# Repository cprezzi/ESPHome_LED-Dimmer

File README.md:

## ESPHome LED-Dimmer

This PCB for crating an ESPHome based LED-Dimmer for 12V LED-Lights was made by KiCad 9.
The PCB is hosting an ESP32-C3 Supermini, a Mini Buck-Converter for 12V > 5V conversion and a Mosfet for PWM-switching the LEDs. 

ESPHome is used as the firmware on the ESP32-C3 (configured as PWM output).

The board is capable of driving LEDs up to 12V/5A.

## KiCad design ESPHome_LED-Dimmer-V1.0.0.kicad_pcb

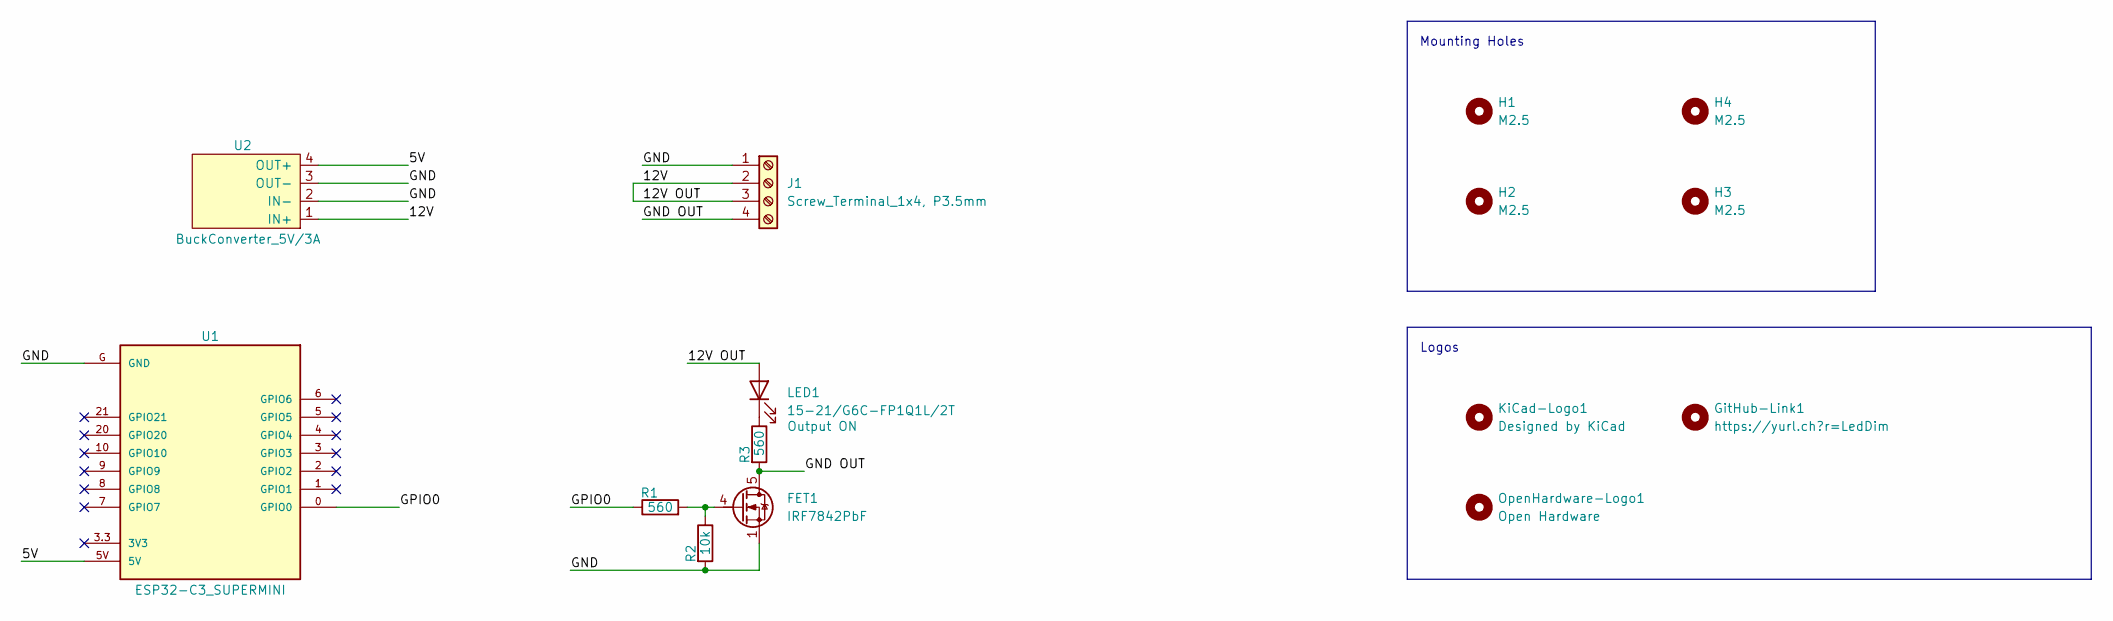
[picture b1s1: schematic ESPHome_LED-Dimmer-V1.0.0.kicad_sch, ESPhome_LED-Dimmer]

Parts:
FET1: IRF7842PbF; SOIC-8_3.9x4.9mm_P1.27mm
GitHub-Link1: https://yurl.ch?r=LedDim; QR_GitHub-LedDim
H1, H2, H3, H4: M2.5; MountingHole_2.2mm_M2
J1: Screw_Terminal_1x4, P3.5mm; TerminalBlock_MetzConnect_Type059_RT06304HBWC_1x04_P3.50mm_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
KiCad-Logo1: Designed by KiCad; KiCad-Logo2_5mm_SilkScreen
LED1: 15-21/G6C-FP1Q1L/2T; LED_1206_3216Metric
OpenHardware-Logo1: Open Hardware; OSHW-Logo2_7.3x6mm_SilkScreen
R1, R3: 560; R_XL_1206_3216Metric_Pad_HandSolder
R2: 10k; R_XL_1206_3216Metric_Pad_HandSolder
U1: ESP32-C3_SUPERMINI; MODULE_ESP32-C3_SUPERMINI_FlatSolder
U2: BuckConverter_5V/3A; Mini BuckConverter 5V 3A

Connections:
/5V: U1.5V, U2.4 (OUT+)
/12V: J1.2, J1.3, LED1.2 (A), U2.1 (IN+)
/GND: FET1.1 (S), FET1.2 (S), FET1.3 (S), J1.1, R2.2, U1.G (GND), U2.2 (IN-), U2.3 (OUT-)
/GND OUT: FET1.5 (D), FET1.6 (D), FET1.7 (D), FET1.8 (D), J1.4, R3.2
/GPIO0: R1.1, U1.0 (GPIO0)
unnamed: FET1.4 (G), R1.2, R2.1
unnamed: LED1.1 (K), R3.1

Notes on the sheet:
Logos
Mounting Holes

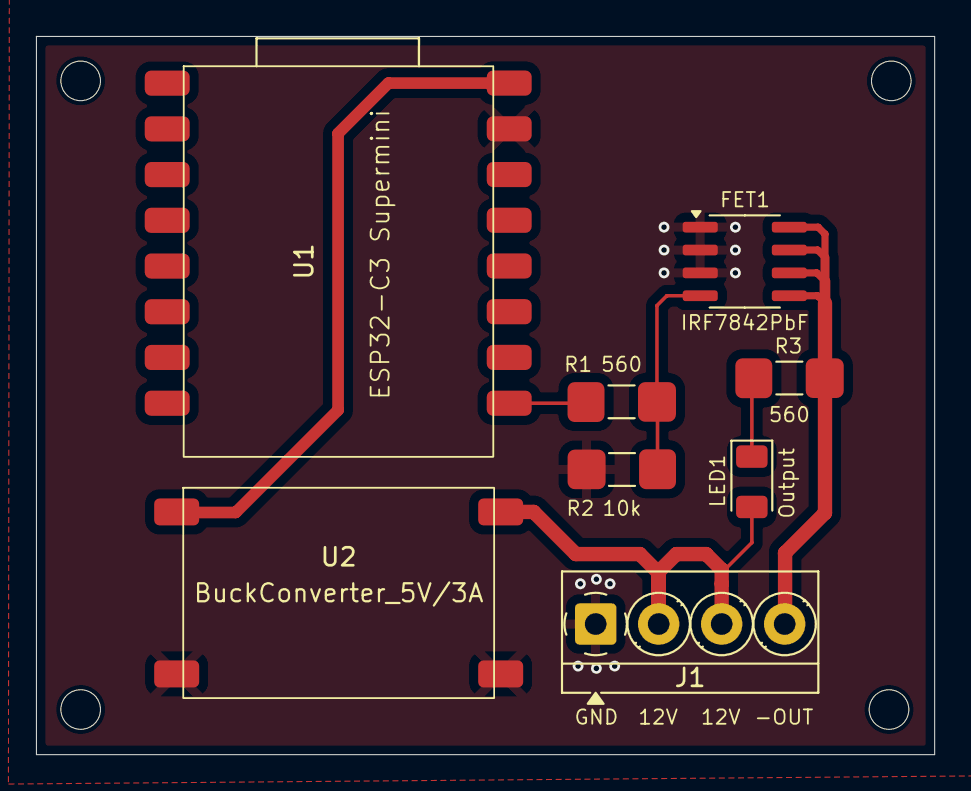
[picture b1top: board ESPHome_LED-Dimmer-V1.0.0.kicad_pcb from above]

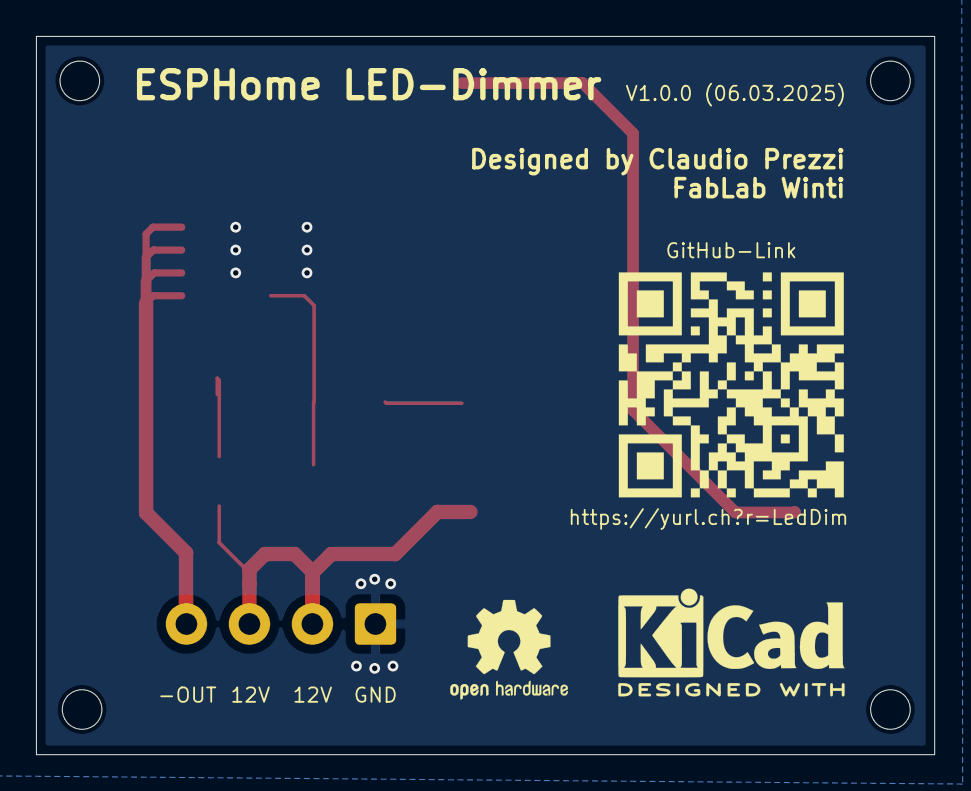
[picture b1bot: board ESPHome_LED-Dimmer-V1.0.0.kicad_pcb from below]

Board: 2 copper layers, 49.9 x 39.9 mm, 15 parts (3 on the bottom side), 7 nets.

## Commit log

2025-02-28 Innitial Commit for ESPHome LED-Driver V1.0.0
2025-02-28 Added pictures of PCB
2025-03-06 Final version 1.0.0 (for PCB production)
2025-03-06 Unused files deleted
2025-03-20 Final version including case for 3d-printing
2025-03-20 RC 1.0.0
2025-03-20 Corrected standoffs for M2.5 inserts
